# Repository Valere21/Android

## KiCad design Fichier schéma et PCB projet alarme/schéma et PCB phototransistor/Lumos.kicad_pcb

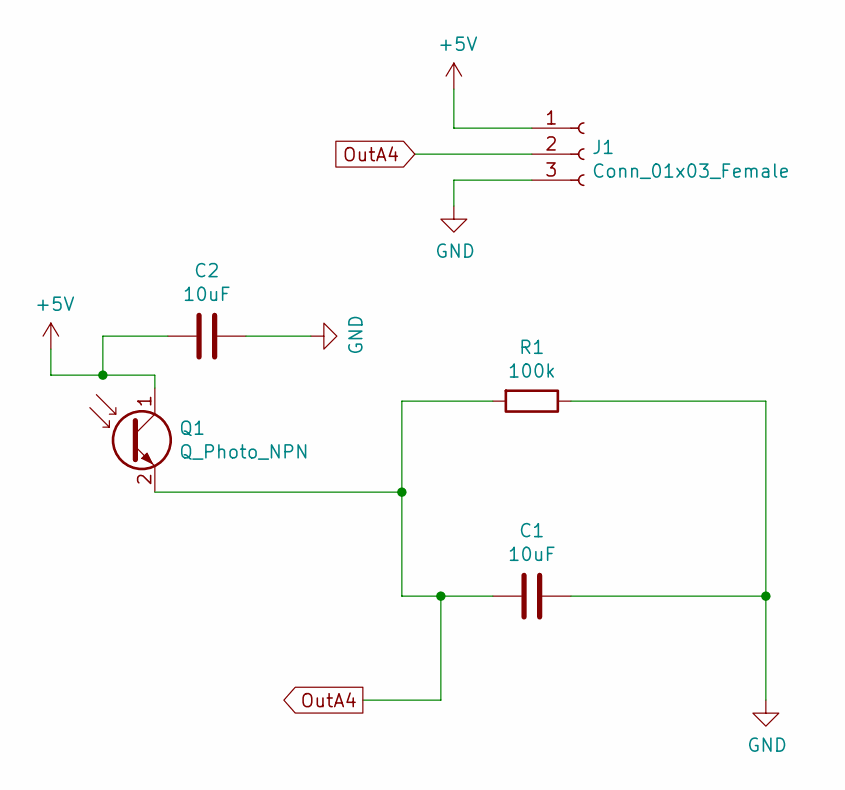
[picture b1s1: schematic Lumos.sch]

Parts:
C1, C2: 10uF; C_Disc_D3.8mm_W2.6mm_P2.50mm
J1: Conn_01x03_Female; PinHeader_1x03_P1.00mm_Horizontal
Q1: Q_Photo_NPN; R_0603_1608Metric_Pad1.05x0.95mm_HandSolder
R1: 100k; R_Axial_DIN0204_L3.6mm_D1.6mm_P5.08mm_Horizontal

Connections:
+5V: C2.2, J1.1, Q1.1 (C)
GND: C1.1, C2.1, J1.3, R1.1
OutA4: C1.2, J1.2, Q1.2 (E), R1.2

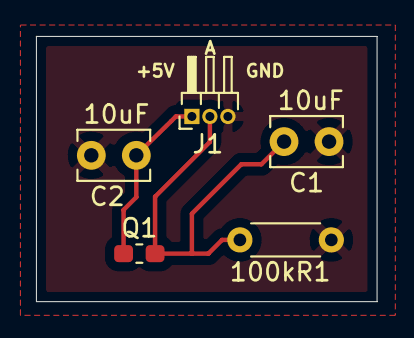
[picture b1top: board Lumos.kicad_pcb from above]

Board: 2 copper layers, 18.9 x 14.7 mm, 5 parts (0 on the bottom side), 3 nets.

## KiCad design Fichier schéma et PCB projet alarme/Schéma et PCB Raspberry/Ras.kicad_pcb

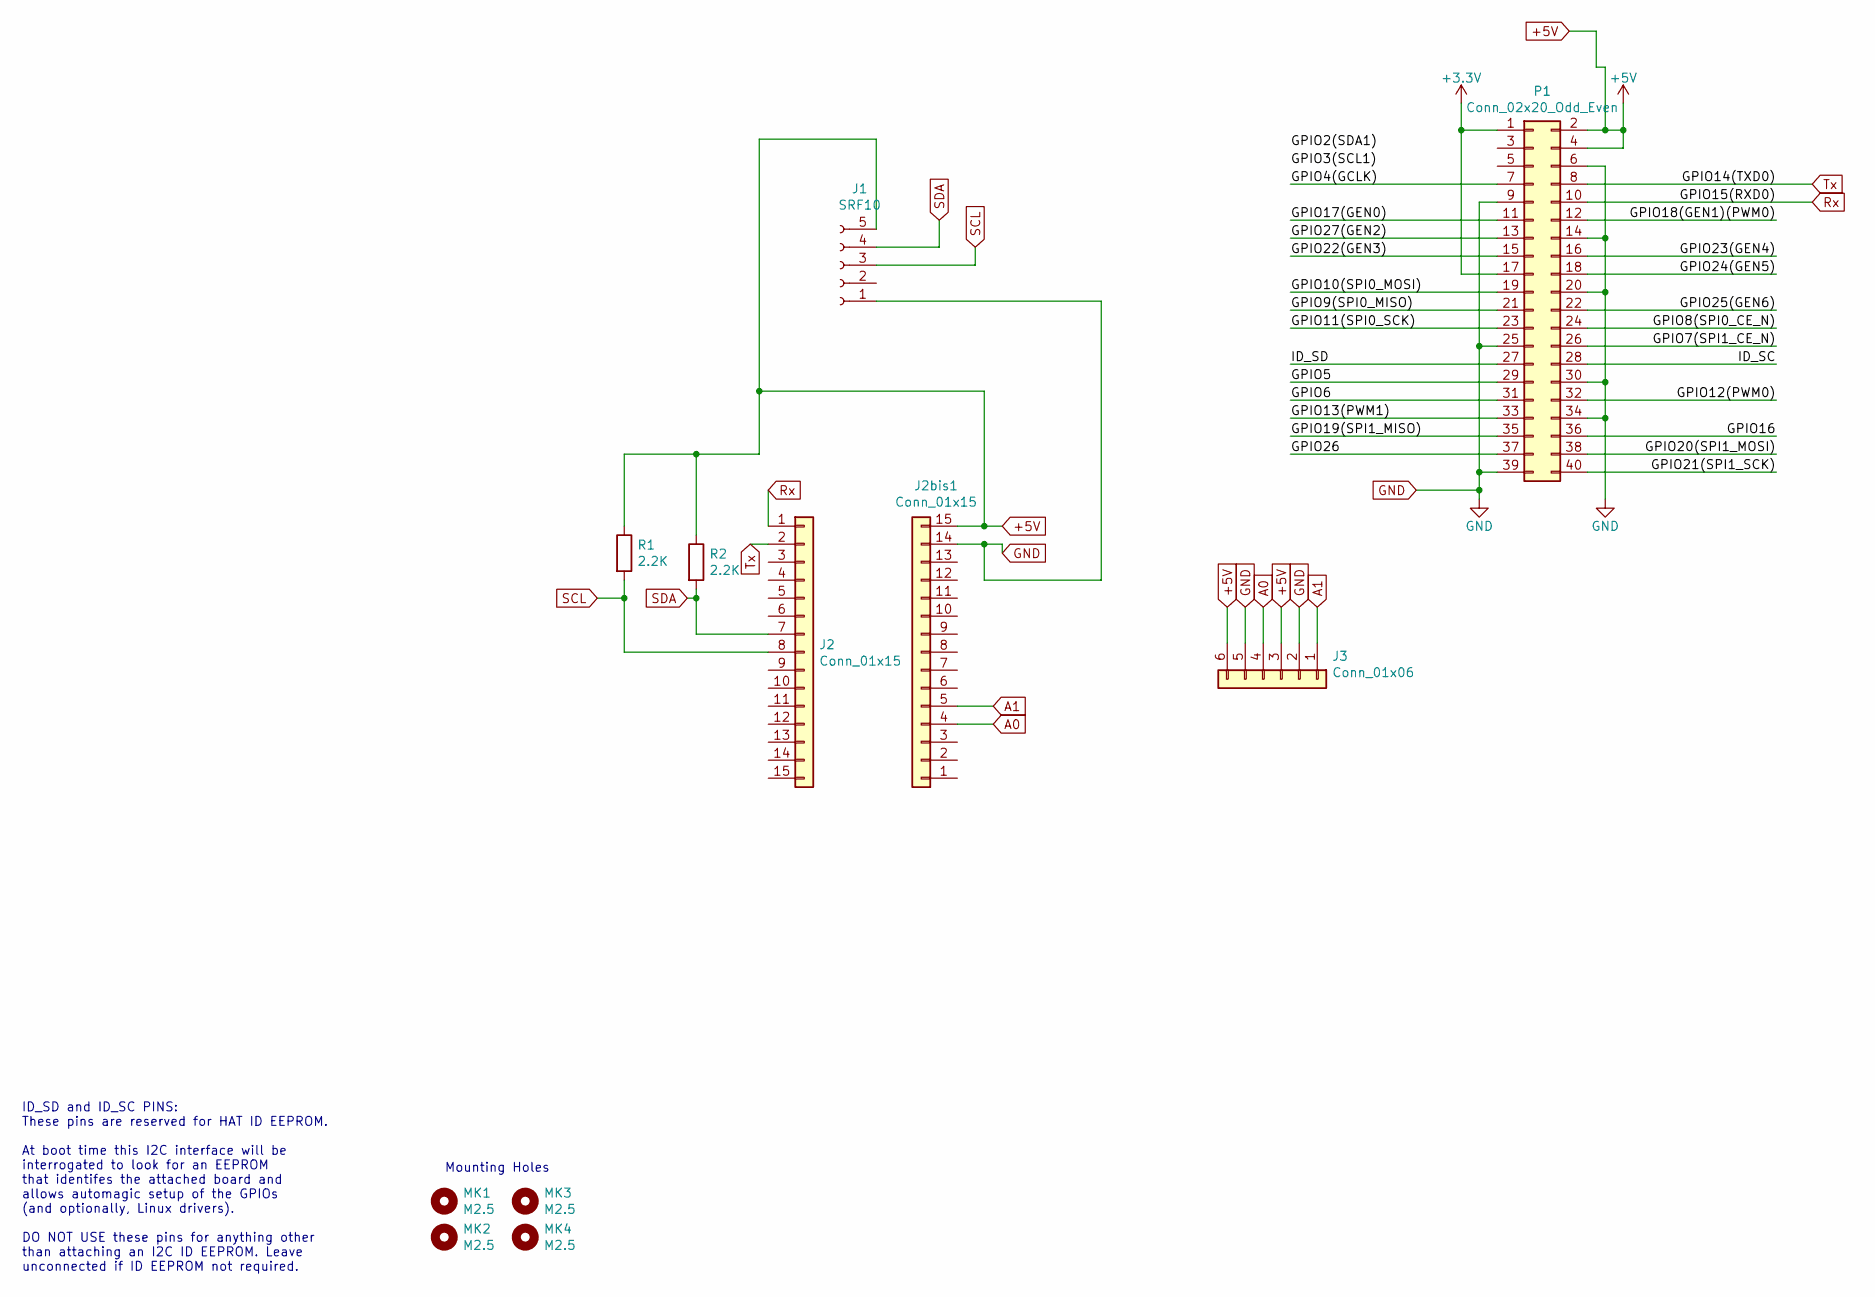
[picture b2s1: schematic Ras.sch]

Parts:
J1: SRF10; PinHeader_1x05_P2.00mm_Vertical
J2, J2bis1: Conn_01x15; PinSocket_1x15_P2.54mm_Vertical
J3: Conn_01x06; PinHeader_1x06_P2.00mm_Vertical
MK1, MK2, MK3, MK4: M2.5; MountingHole_2.7mm_M2.5
P1: Conn_02x20_Odd_Even; PinSocket_2x20_P2.54mm_Vertical
R1, R2: 2.2K; R_1206_3216Metric_Pad1.42x1.75mm_HandSolder

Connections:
+3V3: P1.1, P1.17
+5V: J1.5, J2bis1.15, J3.3, J3.6, P1.2, P1.4, R1.1, R2.1
/GPIO4(GCLK): P1.7
/GPIO5: P1.29
/GPIO6: P1.31
/GPIO7(SPI1_CE_N): P1.26
/GPIO8(SPI0_CE_N): P1.24
/GPIO9(SPI0_MISO): P1.21
/GPIO10(SPI0_MOSI): P1.19
/GPIO11(SPI0_SCK): P1.23
/GPIO12(PWM0): P1.32
/GPIO13(PWM1): P1.33
/GPIO16: P1.36
/GPIO17(GEN0): P1.11
/GPIO18(GEN1)(PWM0): P1.12
/GPIO19(SPI1_MISO): P1.35
/GPIO20(SPI1_MOSI): P1.38
/GPIO21(SPI1_SCK): P1.40
/GPIO22(GEN3): P1.15
/GPIO23(GEN4): P1.16
/GPIO24(GEN5): P1.18
/GPIO25(GEN6): P1.22
/GPIO26: P1.37
/GPIO27(GEN2): P1.13
/ID_SC: P1.28
/ID_SD: P1.27
A0: J2bis1.4, J3.4
A1: J2bis1.5, J3.1
GND: J1.1, J2bis1.14, J3.2, J3.5, P1.6, P1.9, P1.14, P1.20, P1.25, P1.30, P1.34, P1.39
Rx: J2.1, P1.10
SCL: J1.3, J2.8, R1.2
SDA: J1.4, J2.7, R2.2
Tx: J2.2, P1.8

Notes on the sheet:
ID_SD and ID_SC PINS: These pins are reserved for HAT ID EEPROM. At boot time this I2C interface will be interrogated to look for an EEPROM that identifes the attached board and allows automagic setup of the GPIOs (and optionally, Linux drivers). DO NOT USE these pins for anything other than attach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
Mounting Holes

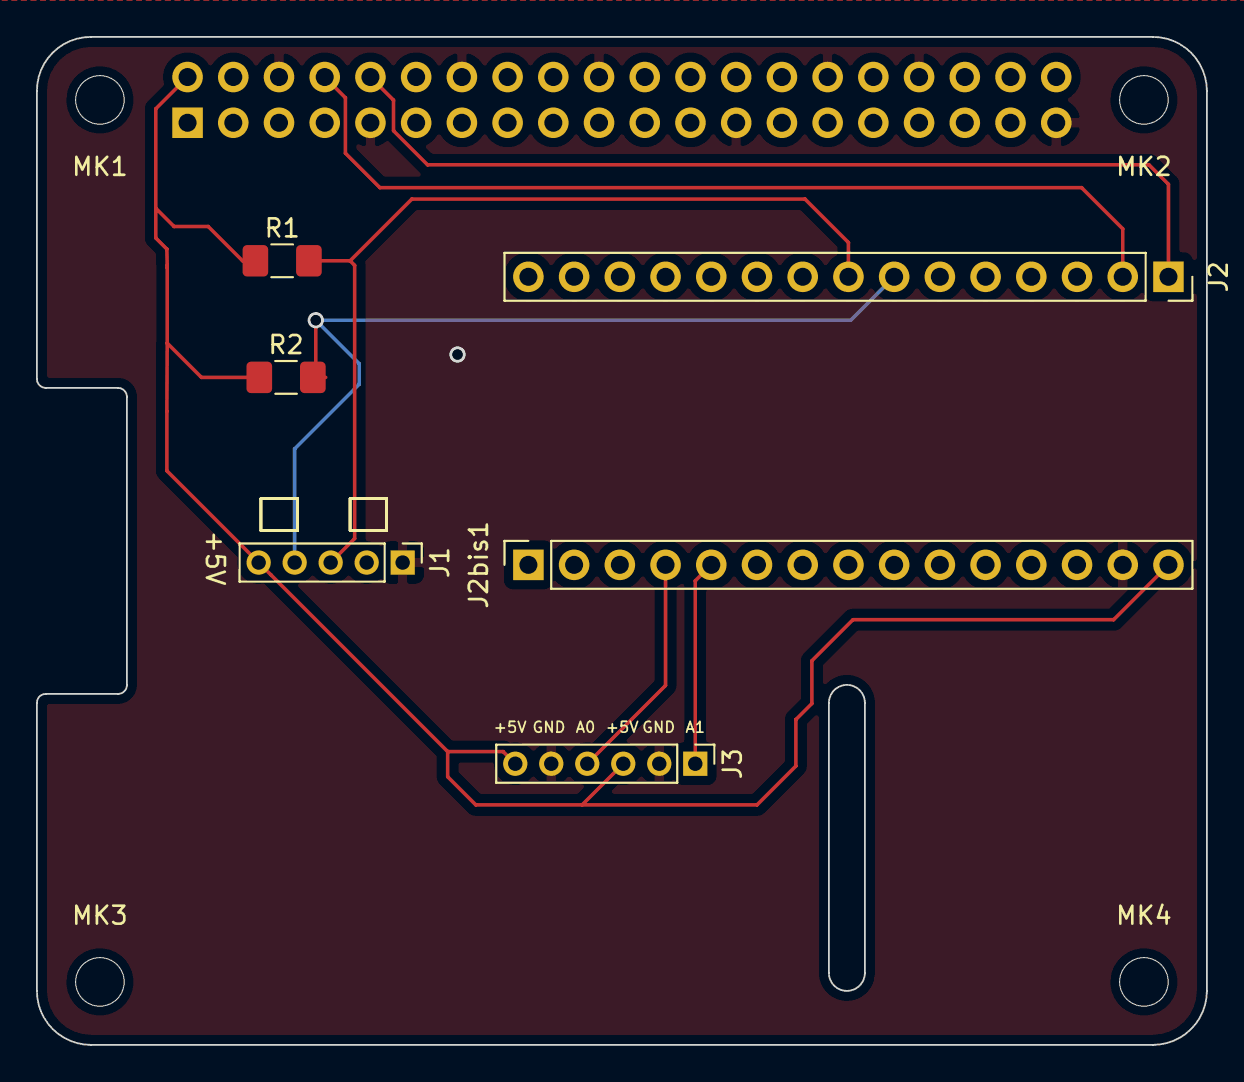
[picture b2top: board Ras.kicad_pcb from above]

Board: 2 copper layers, 65.0 x 56.0 mm, 11 parts (1 on the bottom side), 9 nets.

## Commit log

2020-05-11 Création branche microntrolleur
2020-05-14 Ajout du projet QT
2020-05-27 Image du projet
2020-06-03 Ajout du projet Qt client
2020-06-08 Programme phototransistor nucléo (lecture de 2 capteurs en hysteresis, sans com)
2020-06-08 Programme dans la nucléo
2020-06-08 Programme nucléo
2020-06-08 Image projet
2020-06-16 sprint2
2020-06-17 Code complet nucléo à télécharger
2020-06-17 Programme nucléo à télécharger
2020-06-19 commit avec partie com serie integré au serveur
2020-06-19 debug + build
2020-06-19 correction serveur + com serie
2020-06-22 commit app
2020-06-22 Fichier schéma + PC
2020-06-23 Fichier schéma + PCB à télécharger
2020-06-23 Fichier schéma + PCB
2020-06-24 Image des pièces 3D et fichier STL
2020-06-24 Fichier STL à télécharger
2020-06-24 Pièces 3D imprimé
